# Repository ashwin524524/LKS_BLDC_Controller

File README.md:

A low cost, accessible FOC motor controller for small robotics applications. Rated for ~50v and 40A.

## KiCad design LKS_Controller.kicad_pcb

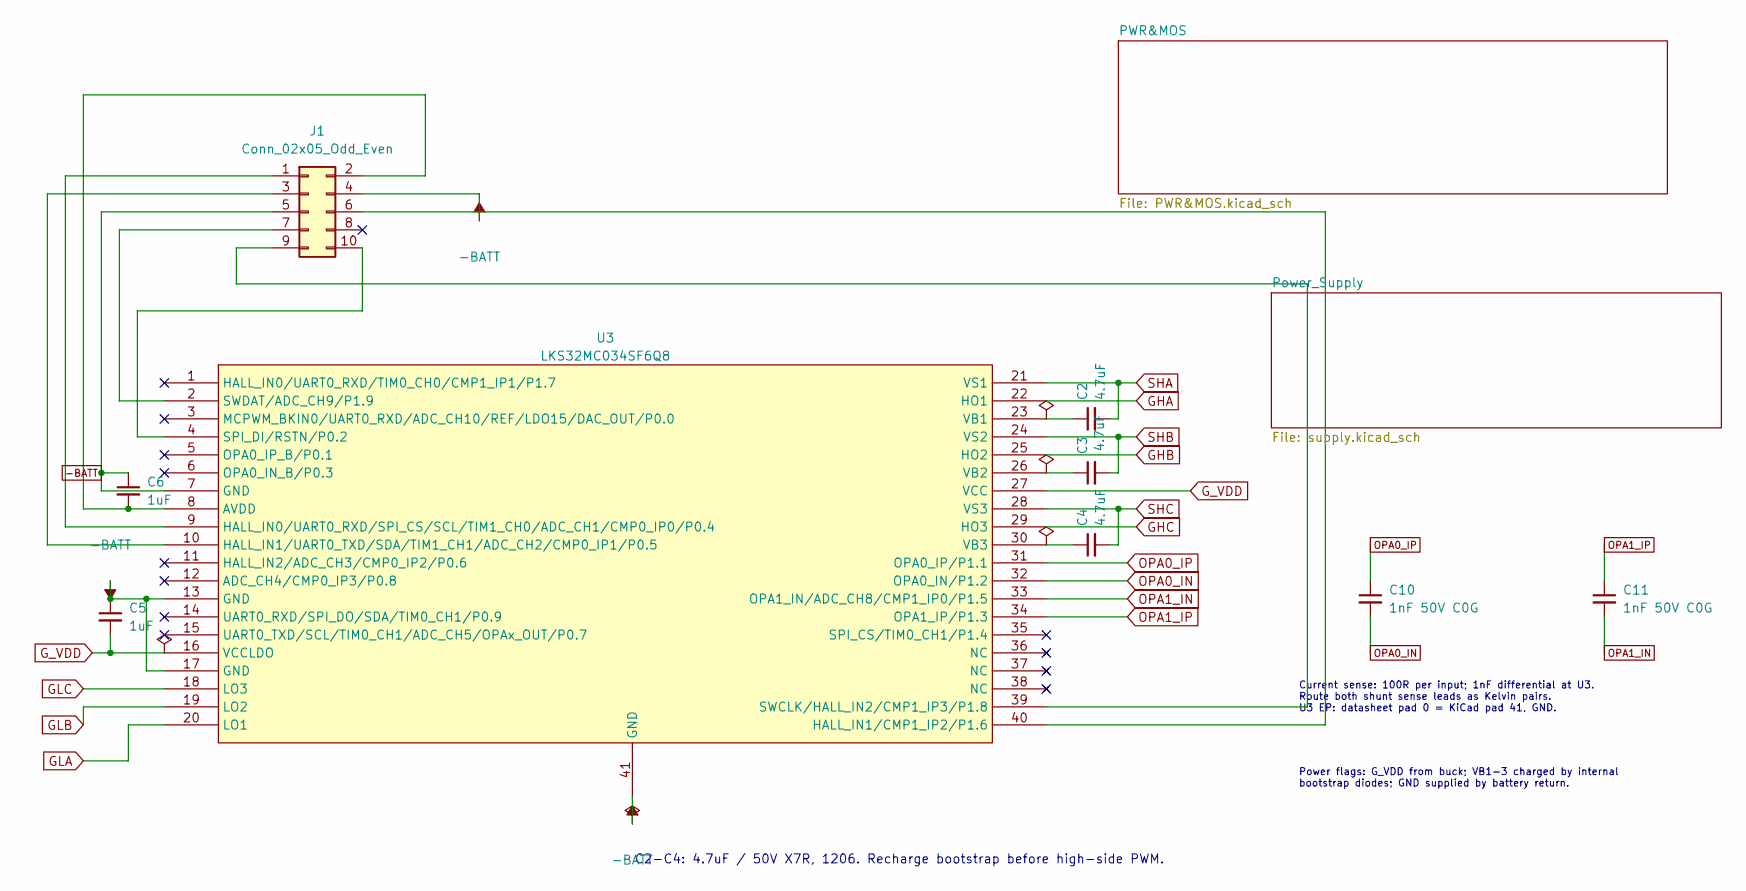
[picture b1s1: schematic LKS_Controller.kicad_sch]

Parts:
C2, C3, C4: 4.7uF; C_1206_3216Metric_Pad1.33x1.80mm_HandSolder; Tolerance 10%; Voltage 50V; MPN CC1206KKX7R9BB475; LCSC C132170
C5, C6: 1uF; C_0603_1608Metric_Pad1.08x0.95mm_HandSolder
C10, C11: 1nF 50V C0G; C_0603_1608Metric_Pad1.08x0.95mm_HandSolder; MPN CC0603KRNPO9BN102; LCSC C3909020
J1: Conn_02x05_Odd_Even; PinSocket_2x05_P2.54mm_Vertical
U3: LKS32MC034SF6Q8; QFN-40-1EP_5x5mm_P0.4mm_EP3.6x3.6mm_ThermalVias; MPN LKS32MC034SF6Q8; LCSC C19193083

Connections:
-BATT: C5.1, C6.1, J1.4, J1.5, U3.7 (GND), U3.13 (GND), U3.17 (GND), U3.41 (GND); also elsewhere on the board
GHA: U3.22 (HO1); also elsewhere on the board
GHB: U3.25 (HO2); also elsewhere on the board
GHC: U3.29 (HO3); also elsewhere on the board
GLA: U3.20 (LO1); also elsewhere on the board
GLB: U3.19 (LO2); also elsewhere on the board
GLC: U3.18 (LO3); also elsewhere on the board
G_VDD: C5.2, U3.16 (VCCLDO), U3.27 (VCC); also elsewhere on the board
unnamed: J1.1, U3.9 (HALL_IN0/UART0_RXD/SPI_CS/SCL/TIM1_CH0/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)
unnamed: C6.2, J1.2, U3.8 (AVDD)
unnamed: J1.3, U3.10 (HALL_IN1/UART0_TXD/SDA/TIM1_CH1/ADC_CH2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)
unnamed: J1.6, U3.40 (HALL_IN1/CMP1_IP2/P1.6)
unnamed: J1.7, U3.2 (SWDAT/ADC_CH9/P1.9)
unnamed: J1.9, U3.39 (SWCLK/HALL_IN2/CMP1_IP3/P1.8)
unnamed: J1.10, U3.4 (SPI_DI/RSTN/P0.2)
unnamed: C2.1, U3.23 (VB1)
unnamed: C3.1, U3.26 (VB2)
unnamed: C4.1, U3.30 (VB3)
OPA0_IN: C10.2, U3.32 (OPA0_IN/P1.2); also elsewhere on the board
OPA0_IP: C10.1, U3.31 (OPA0_IP/P1.1); also elsewhere on the board
OPA1_IN: C11.2, U3.33 (OPA1_IN/ADC_CH8/CMP1_IP0/P1.5); also elsewhere on the board
OPA1_IP: C11.1, U3.34 (OPA1_IP/P1.3); also elsewhere on the board
SHA: C2.2, U3.21 (VS1); also elsewhere on the board
SHB: C3.2, U3.24 (VS2); also elsewhere on the board
SHC: C4.2, U3.28 (VS3); also elsewhere on the board

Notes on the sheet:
C2-C4: 4.7uF / 50V X7R, 1206. Recharge bootstrap before high-side PWM.
Current sense: 100R per input; 1nF differential at U3. Route both shunt sense leads as Kelvin pairs. U3 EP: datasheet pad 0 = KiCad pad 41, GND.
Power flags: G_VDD from buck; VB1-3 charged by internal bootstrap diodes; GND supplied by battery return.

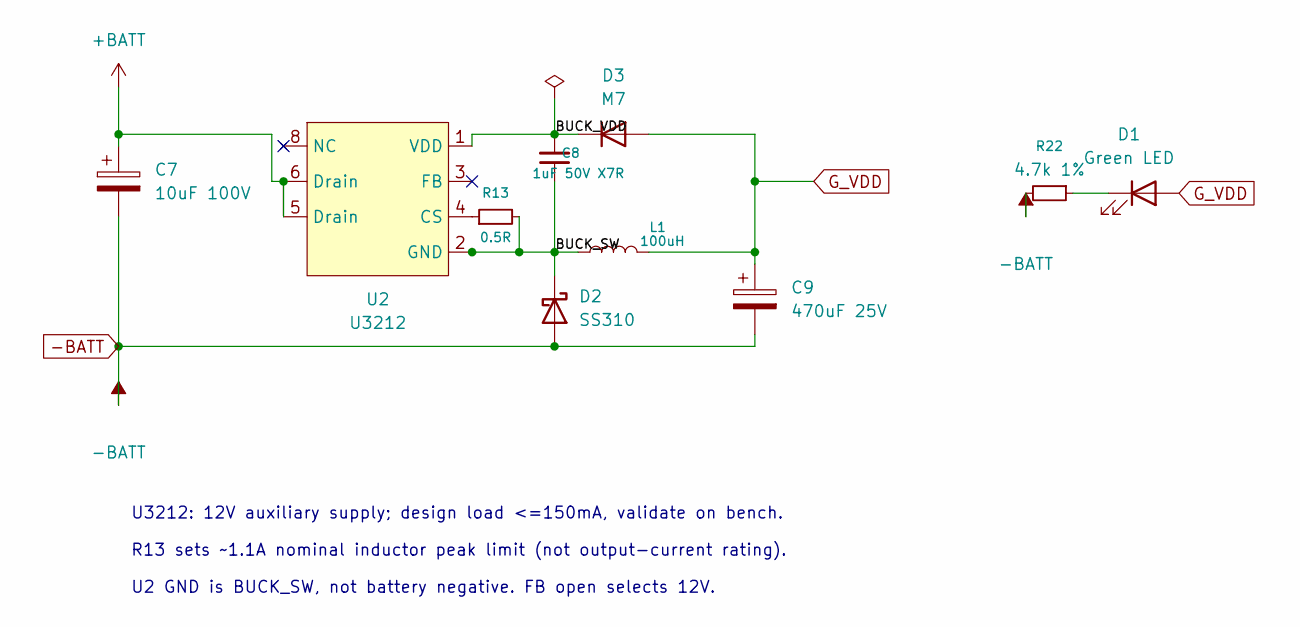
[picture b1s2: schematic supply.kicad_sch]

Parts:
C7: 10uF 100V; C_Radial_D6.3mm_H11.0mm_P2.50mm; MPN ERS1KM100E11OT; LCSC C106677
C8: 1uF 50V X7R; C_0805_2012Metric_Pad1.18x1.45mm_HandSolder; MPN TCC0805X7R105M500FT; LCSC C376929
C9: 470uF 25V; C_Radial_D8.0mm_H12.0mm_P3.50mm; MPN 01EC1227SHC470UF25V; LCSC C503221
D1: Green LED; LED_0603_1608Metric_Pad1.05x0.95mm_HandSolder; MPN 19-217/GHC-YR1S2/3T; LCSC C72043
D2: SS310; D_SMA; MPN SS310; LCSC C513470
D3: M7; D_SMA; MPN M7; LCSC C266550
L1: 100uH; L_XR_XR0650; MPN XR0650-101M; LCSC C5358146
R13: 0.5R; R_1206_3216Metric_Pad1.30x1.75mm_HandSolder; MPN HP06W2F500LT5E; LCSC C2759131
R22: 4.7k 1%; R_0603_1608Metric_Pad0.98x0.95mm_HandSolder; MPN 0603WAF4701T5E; LCSC C23162
U2: U3212; U3212_SOP-7_3.9x4.9mm_P1.27mm; MPN U3212; LCSC C2874740

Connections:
+BATT: C7.1, U2.5 (Drain), U2.6 (Drain); also elsewhere on the board
-BATT: C7.2, C9.2, D2.2 (A), R22.2; also elsewhere on the board
/Power_Supply/BUCK_SW: C8.1, D2.1 (K), L1.1, R13.2, U2.2 (GND)
/Power_Supply/BUCK_VDD: C8.2, D3.1 (K), U2.1 (VDD)
G_VDD: C9.1, D1.2 (A), D3.2 (A), L1.2; also elsewhere on the board
unnamed: D1.1 (K), R22.1
unnamed: R13.1, U2.4 (CS)

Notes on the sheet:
U3212: 12V auxiliary supply; design load <=150mA, validate on bench.
R13 sets ~1.1A nominal inductor peak limit (not output-current rating).
U2 GND is BUCK_SW, not battery negative. FB open selects 12V.

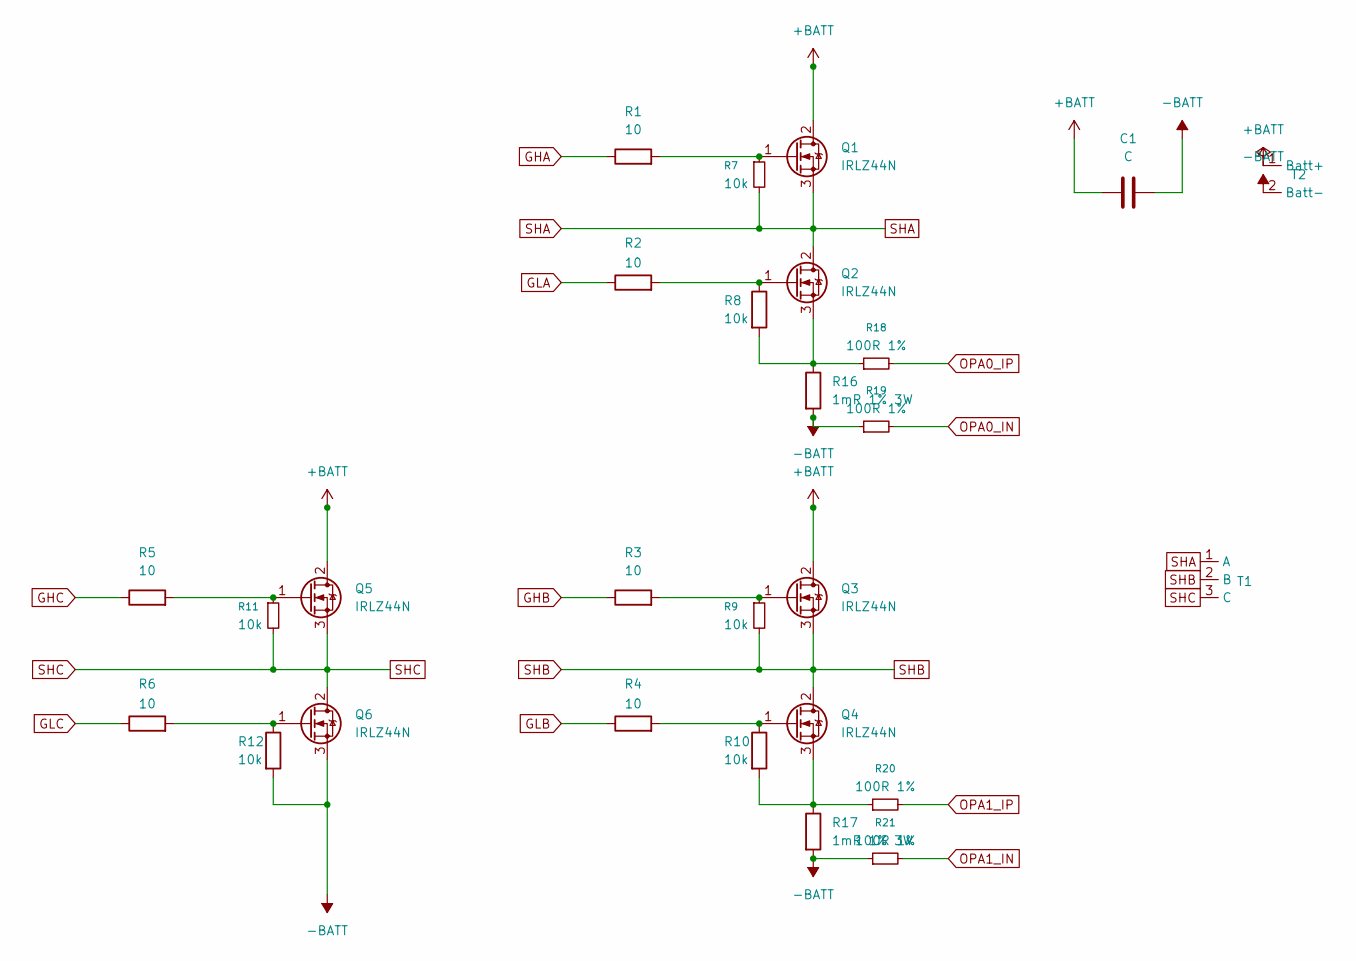
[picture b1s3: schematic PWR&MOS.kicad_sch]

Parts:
C1: C; C_Radial_P5mm_AsRouted
Q1, Q2, Q3, Q4, Q5, Q6: IRLZ44N; TO-220-3_Vertical
R1, R2, R3, R4, R5, R6: 10; R_1206_3216Metric_Pad1.30x1.75mm_HandSolder
R7, R8, R9, R10, R11, R12: 10k; R_0402_1005Metric_Pad0.72x0.64mm_HandSolder; Tolerance 1%; MPN 0402WGF1002TCE; LCSC C25744
R16, R17: 1mR 1% 3W; R_2512_6332Metric; MPN HoJLR2512-3W-1mR-1%; LCSC C2903470
R18, R19, R20, R21: 100R 1%; R_0603_1608Metric_Pad0.98x0.95mm_HandSolder; MPN 0603WAF1000T5E; LCSC C22775
T1: ABC_Terminal
T2: Battery_Wire_Pads_P10mm

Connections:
+BATT: C1.1, Q1.2 (D), Q3.2 (D), Q5.2 (D), T2.1 (Batt+); also elsewhere on the board
-BATT: C1.2, Q6.3 (S), R12.2, R16.2, R17.2, R19.1, R21.1, T2.2 (Batt-); also elsewhere on the board
GHA: R1.1; also elsewhere on the board
GHB: R3.1; also elsewhere on the board
GHC: R5.1; also elsewhere on the board
GLA: R2.1; also elsewhere on the board
GLB: R4.1; also elsewhere on the board
GLC: R6.1; also elsewhere on the board
unnamed: Q1.1 (G), R1.2, R7.1
unnamed: Q2.1 (G), R2.2, R8.1
unnamed: Q2.3 (S), R8.2, R16.1, R18.1
unnamed: Q3.1 (G), R3.2, R9.1
unnamed: Q4.1 (G), R4.2, R10.1
unnamed: Q4.3 (S), R10.2, R17.1, R20.1
unnamed: Q5.1 (G), R5.2, R11.1
unnamed: Q6.1 (G), R6.2, R12.1
OPA0_IN: R19.2; also elsewhere on the board
OPA0_IP: R18.2; also elsewhere on the board
OPA1_IN: R21.2; also elsewhere on the board
OPA1_IP: R20.2; also elsewhere on the board
SHA: Q1.3 (S), Q2.2 (D), R7.2, T1.1 (A); also elsewhere on the board
SHB: Q3.3 (S), Q4.2 (D), R9.2, T1.2 (B); also elsewhere on the board
SHC: Q5.3 (S), Q6.2 (D), R11.2, T1.3 (C); also elsewhere on the board

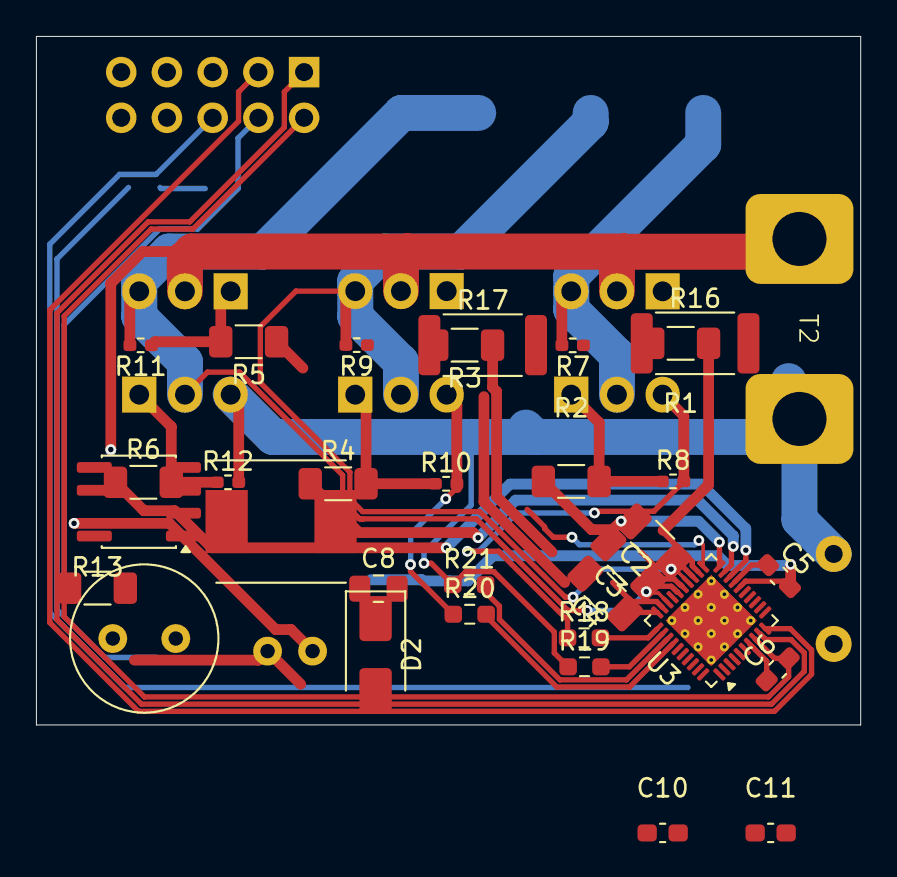
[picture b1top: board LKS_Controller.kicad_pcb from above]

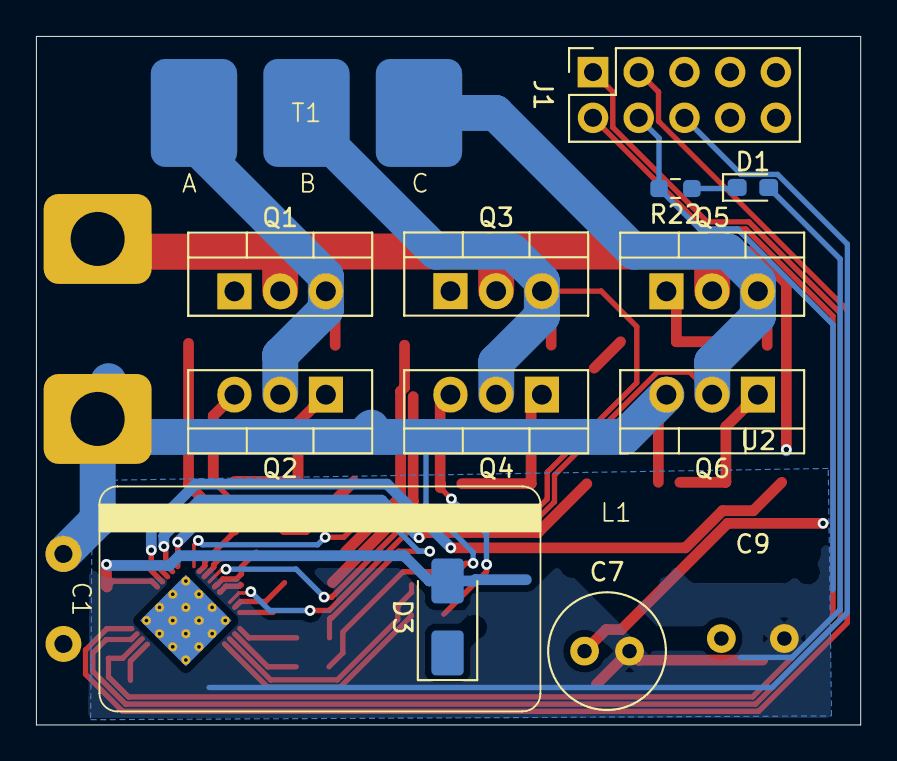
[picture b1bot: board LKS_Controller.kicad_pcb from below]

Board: 2 copper layers, 45.8 x 38.2 mm, 46 parts (13 on the bottom side), 38 nets.
